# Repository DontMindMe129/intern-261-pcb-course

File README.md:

# intern-261-pcb-course

Thiết kế **ESP32-P4 DevKit** cho bài thực hành PCB. Board sử dụng **ESP32-P4 rev 1.3** làm bộ xử lý chính và **ESP32-C6** cho Wi-Fi và Bluetooth LE. PCB có **4 lớp**, kích thước **100 × 70 mm** và độ dày danh định **1,6 mm**.

## Cổng kết nối

| Cổng | Chức năng |
|---|---|
| J3 · USB-C | Nhận nguồn 5 V từ adapter |
| J5 · USB-C | Nạp và debug P4 qua USB Serial/JTAG. VBUS cũng là một đầu vào của bộ chọn nguồn. |
| J11 · USB-C | USB 2.0 High-Speed cho dữ liệu |
| J1 · Header UART | Nạp và debug ESP32-C6 |
| J4 · FFC 15 chân | Camera qua MIPI CSI-2 |
| J6 · FFC 15 chân | Màn hình qua MIPI DSI |
| J2 · microSD | Thẻ nhớ qua SDMMC 4-bit |
| J9 · RJ45 | Ethernet 10/100 qua PHY IP101GRI |
| J10 · Header loa | Loa ngoài qua ampli NS4150B |
| J7 · Header 2×12 | 13 GPIO, I²C, 3V3, 5V_SYS và GND |

Board còn có flash QSPI 16 MB, micro electret, codec ES8311, cảm biến ánh sáng VEML7700 và mạch INA226 đo dòng, áp trên nguồn hệ thống.

## Mở project KiCad

1. Dùng **KiCad 10** và cài gói **Espressif Library** qua **Plugin and Content Manager** để KiCad tra được thư viện Espressif. [Hướng dẫn cài của Espressif](https://github.com/espressif/kicad-libraries#installation-with-kicad-pcm)
2. Mở [esp32_p4_devkit.kicad_pro](hardware/esp32_p4_devkit/esp32_p4_devkit.kicad_pro) trong KiCad Project Manager. Đây là project chính để mở cả schematic và PCB.
3. Giữ nguyên cấu trúc thư mục project. `sym-lib-table` và `fp-lib-table` trỏ tới thư viện `DevKit` trong [libraries/](hardware/esp32_p4_devkit/libraries/).

## Hồ sơ thiết kế

| File | Nội dung |
|---|---|
| [BOM.xlsx](BOM.xlsx) | Danh sách linh kiện, footprint, nguồn mua và sheet DNP |
| [Sơ đồ khối Draw.io](block_diagram/esp32-p4_tong-hop.drawio) | Bản chỉnh sửa được. Xem trang **Bản hiện hành**. |
| [Tài liệu thiết kế](ESP32-P4_Hardware_Design.md) | Kiến trúc, đường nguồn, giao tiếp và bố trí PCB |
| [Design Tracker](ESP32-P4_Design_Tracker.md) | Các mục cần xác nhận trước khi đặt linh kiện, gia công và thử board |

## Trạng thái

Schematic, layout và BOM đã có trong bộ thiết kế. Cần rà ERC/DRC trên bản KiCad chính và xuất Gerber cùng file khoan từ revision chốt để gia công. Chưa có kết quả thử trên board thực.

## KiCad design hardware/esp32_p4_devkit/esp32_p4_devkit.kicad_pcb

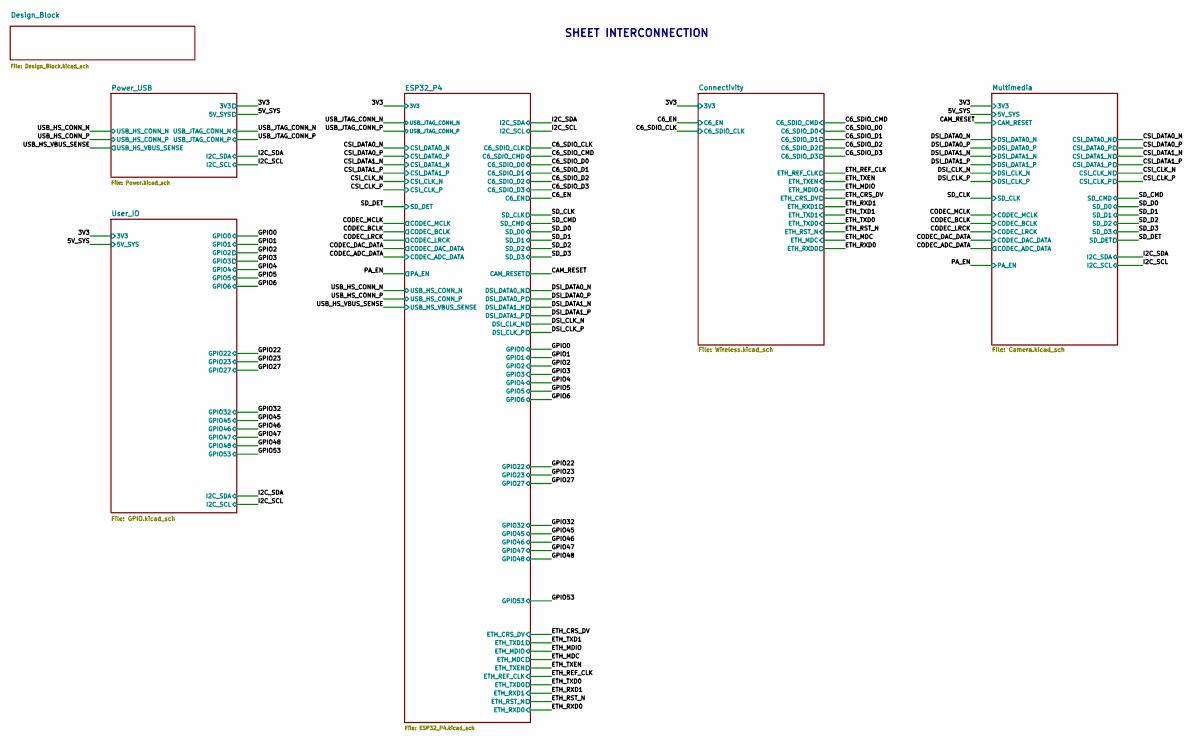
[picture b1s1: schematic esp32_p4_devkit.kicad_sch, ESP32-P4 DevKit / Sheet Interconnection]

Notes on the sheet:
SHEET INTERCONNECTION

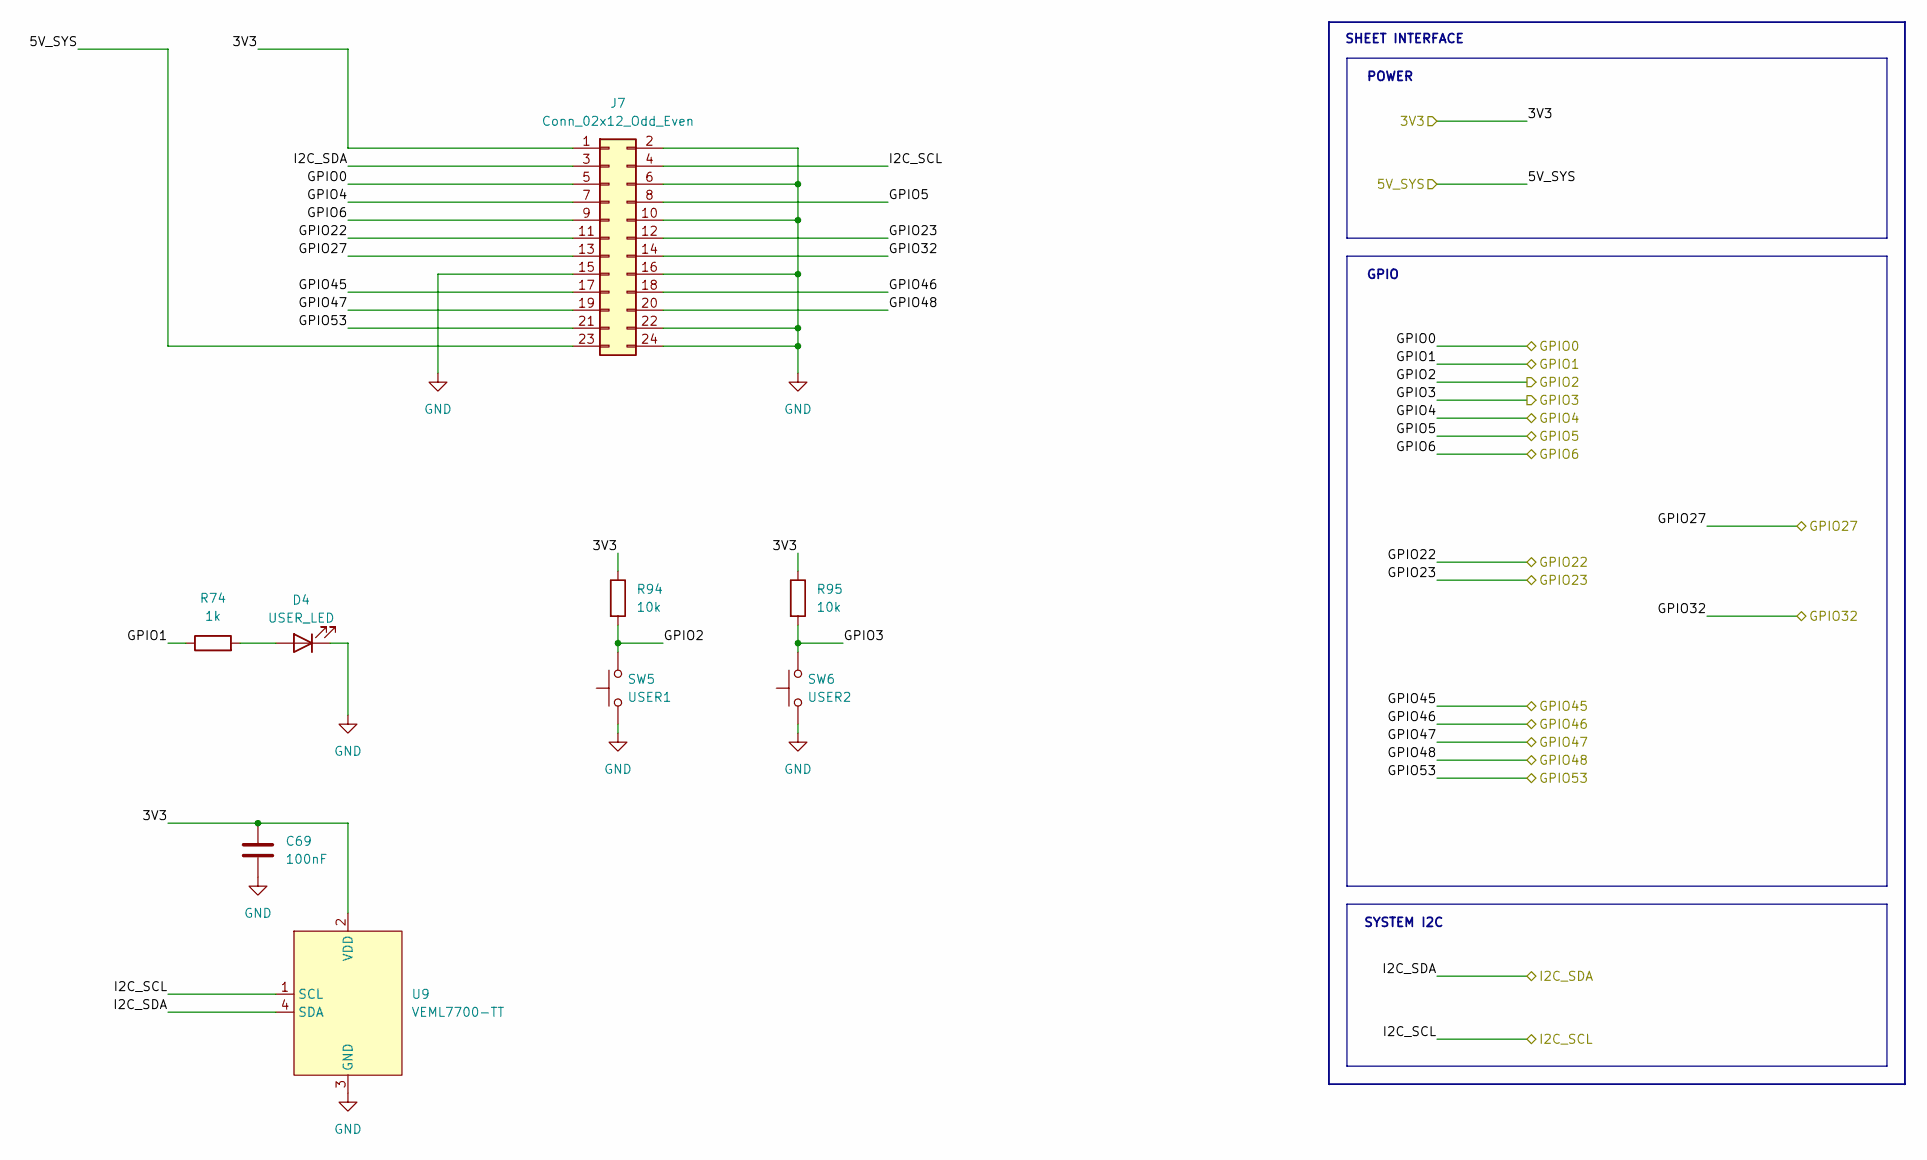
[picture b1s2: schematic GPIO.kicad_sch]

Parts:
C69: 100nF; C_0402_1005Metric; MPN CL05B104KO5NNNC
D4: USER_LED; LED_0603_1608Metric; MPN LTST-C190KGKT
J7: Conn_02x12_Odd_Even; PinHeader_2x12_P2.54mm_Vertical
R74: 1k; R_0603_1608Metric; MPN ERJ-3EKF1001V
R94, R95: 10k; R_0603_1608Metric; MPN ERJ-3EKF1002V
SW5: USER1; SW_SPST_TL3305A; MPN TL3305AF160QG
SW6: USER2; SW_SPST_TL3305A; MPN TL3305AF160QG
U9: VEML7700-TT; SMT_L7700-TT_VIS; MPN VEML7700-TT

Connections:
/3V3: C69.1, J7.1, R94.1, R95.1, U9.2 (VDD); also elsewhere on the board
/5V_SYS: J7.23; also elsewhere on the board
/GPIO0: J7.5; also elsewhere on the board
/GPIO1: R74.1; also elsewhere on the board
/GPIO2: R94.2, SW5.2; also elsewhere on the board
/GPIO3: R95.2, SW6.2; also elsewhere on the board
/GPIO4: J7.7; also elsewhere on the board
/GPIO5: J7.8; also elsewhere on the board
/GPIO6: J7.9; also elsewhere on the board
/GPIO22: J7.11; also elsewhere on the board
/GPIO23: J7.12; also elsewhere on the board
/GPIO27: J7.13; also elsewhere on the board
/GPIO32: J7.14; also elsewhere on the board
/GPIO45: J7.17; also elsewhere on the board
/GPIO46: J7.18; also elsewhere on the board
/GPIO47: J7.19; also elsewhere on the board
/GPIO48: J7.20; also elsewhere on the board
/GPIO53: J7.21; also elsewhere on the board
/I2C_SCL: J7.4, U9.1 (SCL); also elsewhere on the board
/I2C_SDA: J7.3, U9.4 (SDA); also elsewhere on the board
GND: C69.2, D4.1 (K), J7.2, J7.6, J7.10, J7.15, J7.16, J7.22, J7.24, SW5.1, SW6.1, U9.3 (GND); also elsewhere on the board
unnamed: D4.2 (A), R74.2

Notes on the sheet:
SHEET INTERFACE
GPIO
POWER
SYSTEM I2C

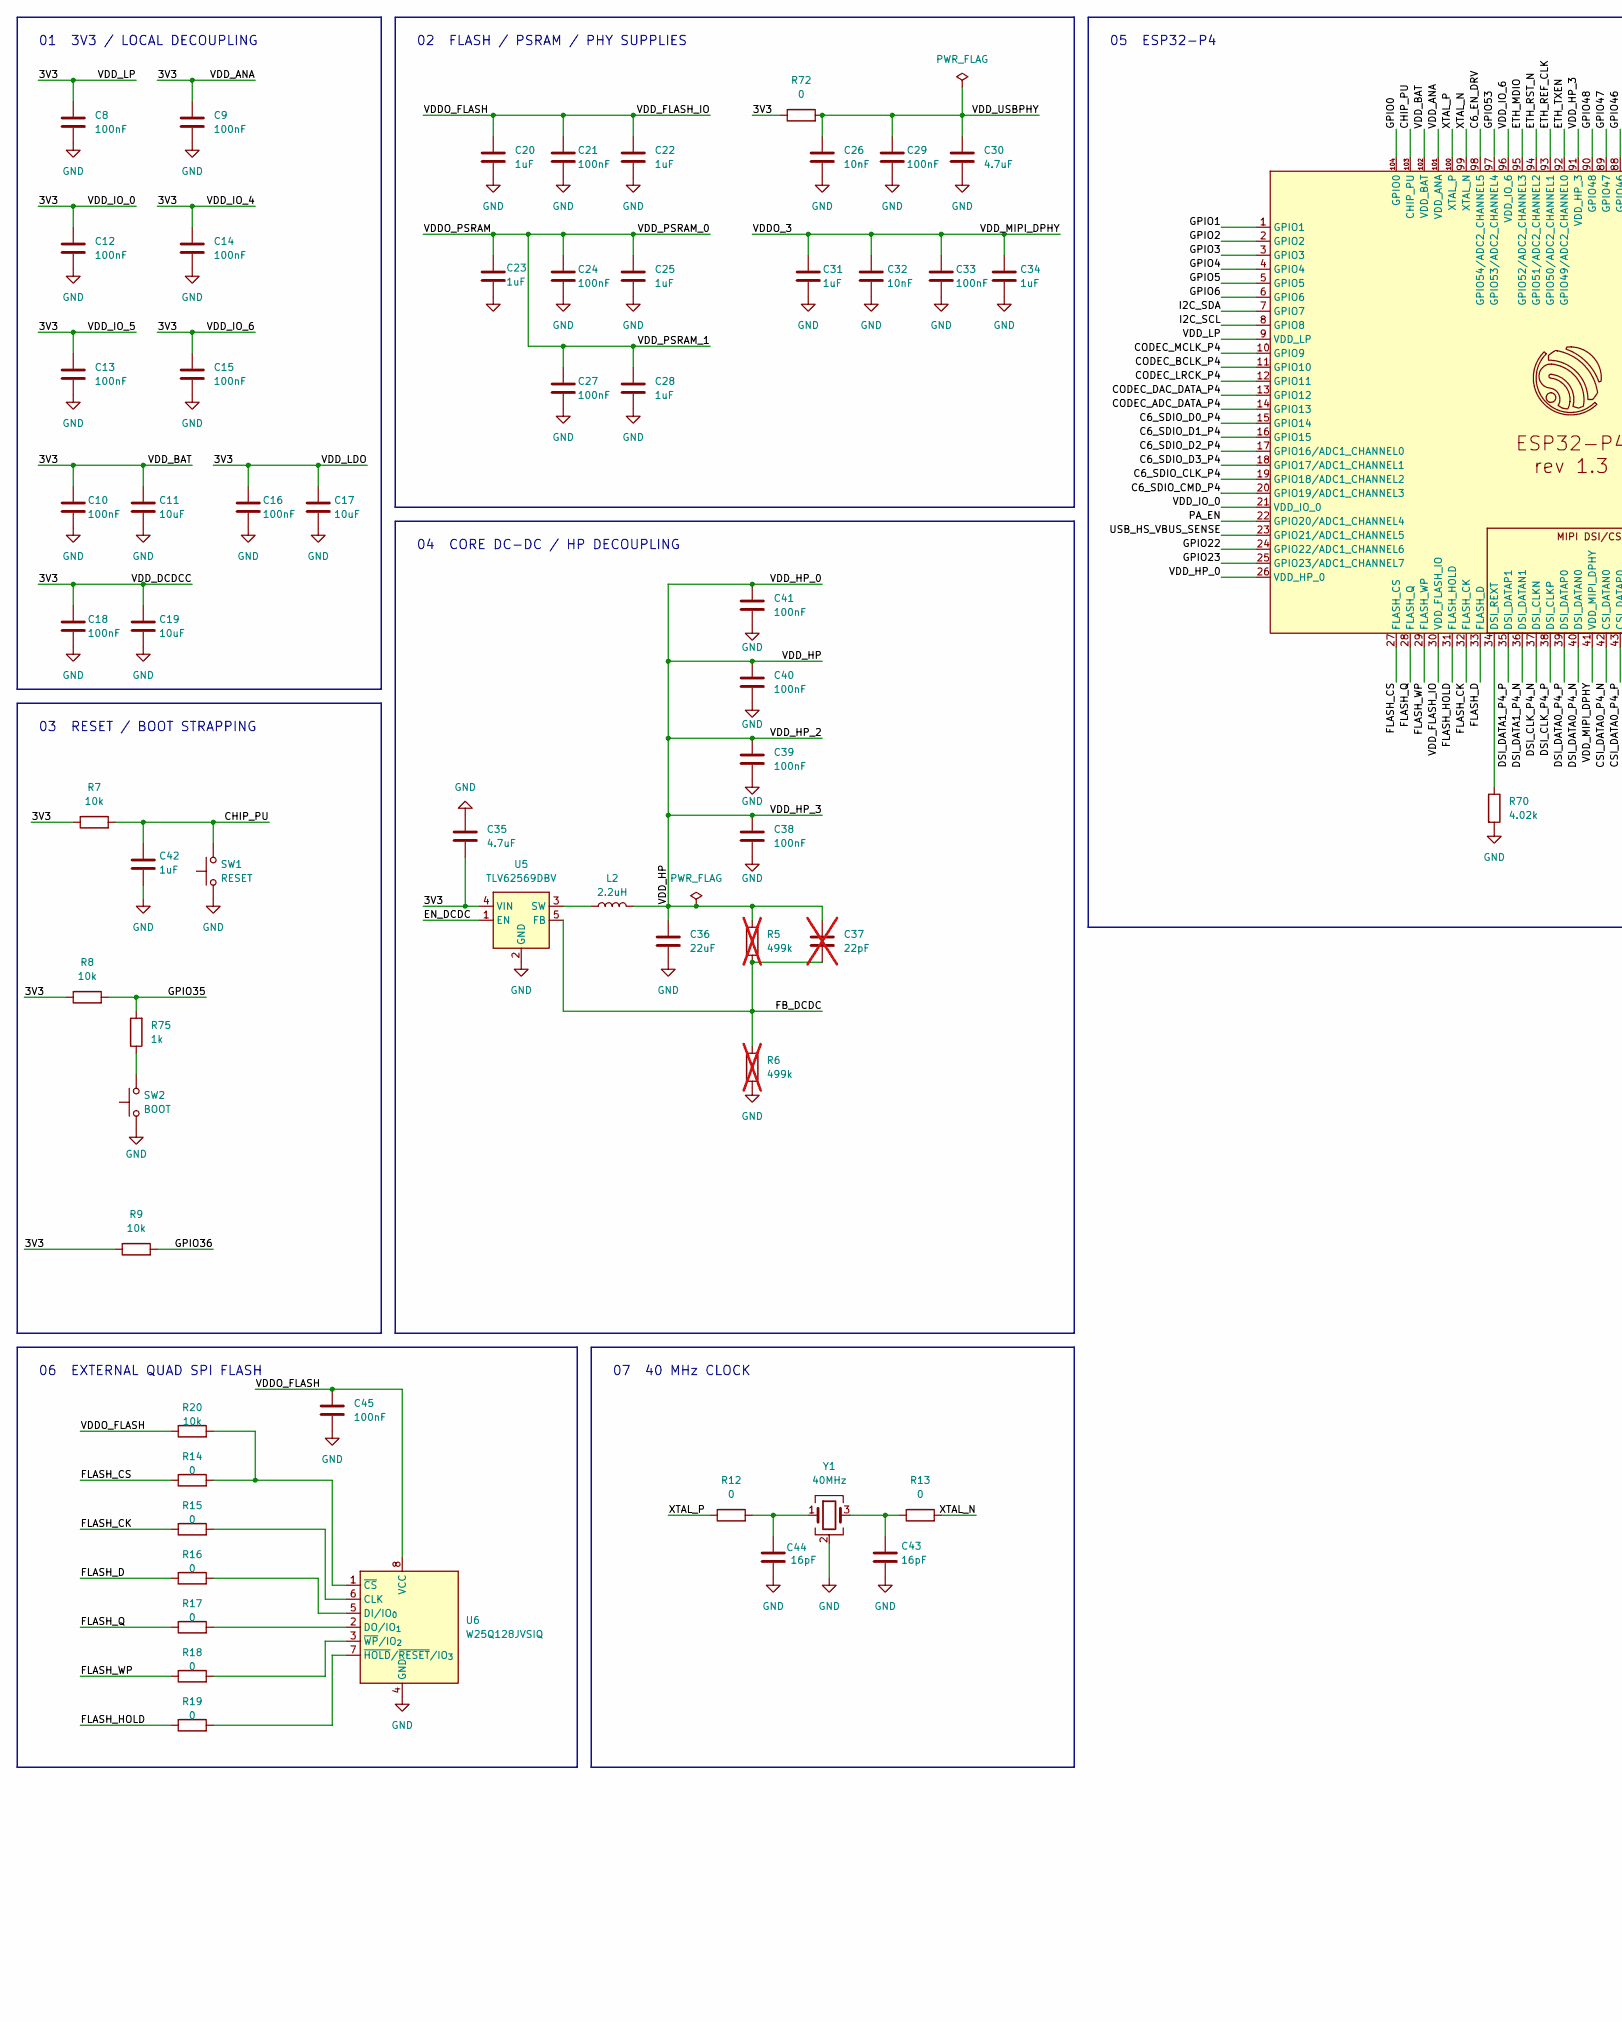
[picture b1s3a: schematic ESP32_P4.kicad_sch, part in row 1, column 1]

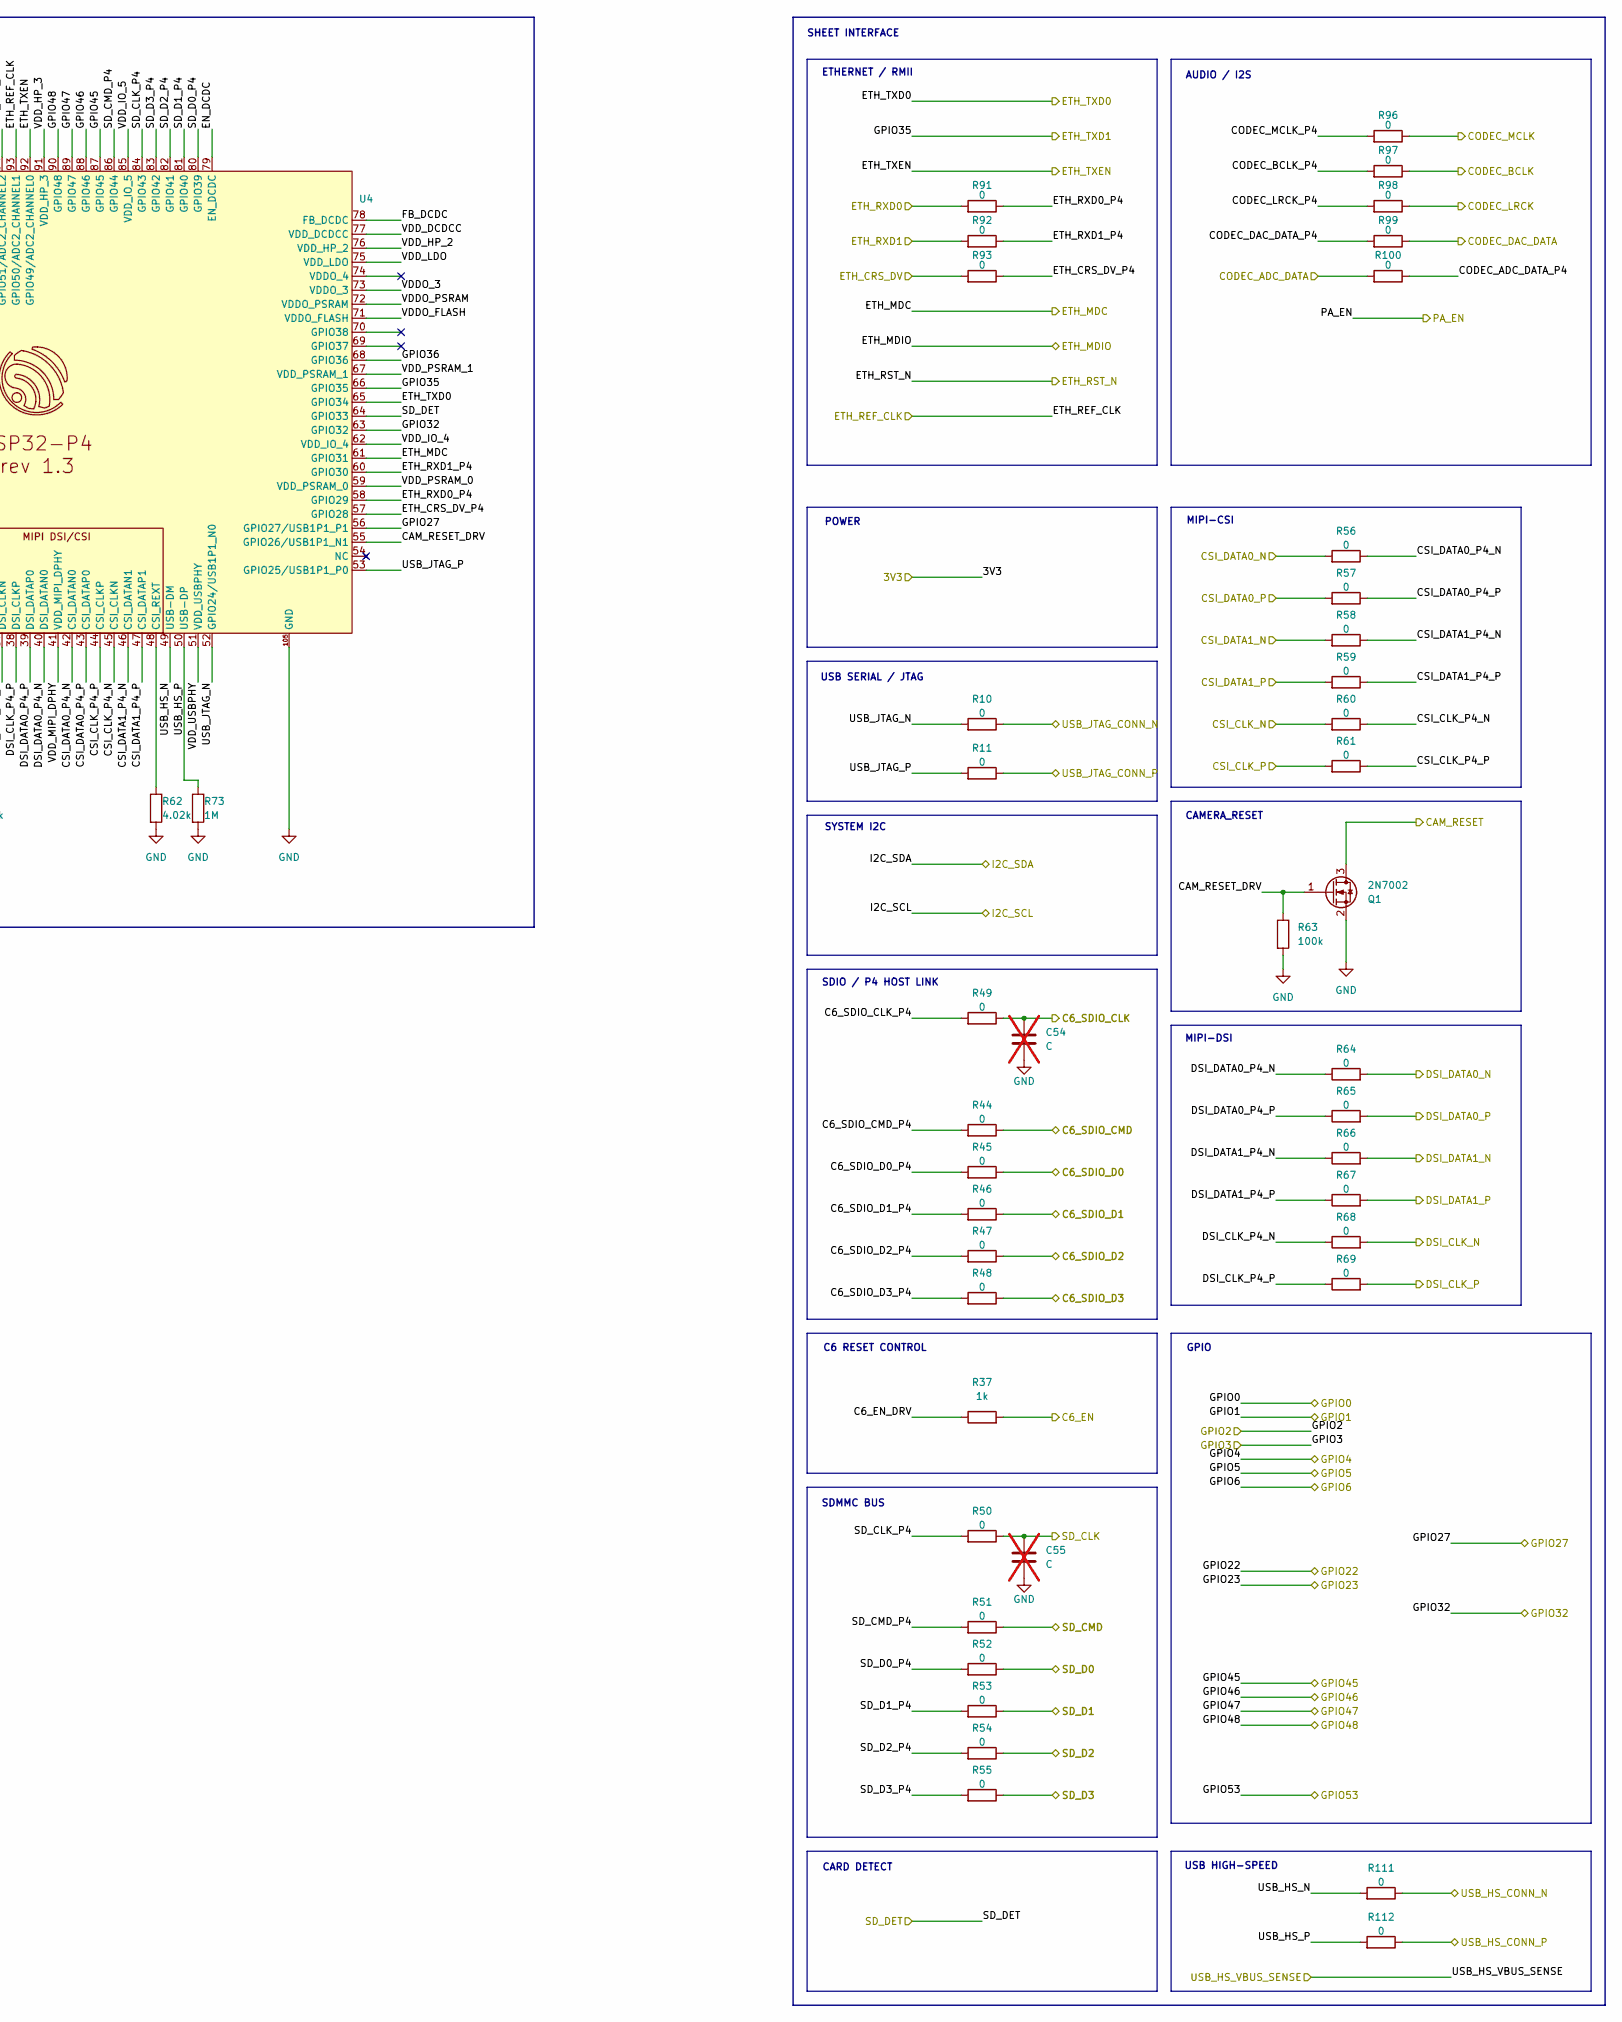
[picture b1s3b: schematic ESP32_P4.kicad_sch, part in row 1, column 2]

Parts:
C8, C9, C10, C12, C13, C14, C15, C16, C18, C21, C24, C27, C29, C33, C38, C40, C41, C45: 100nF; C_0402_1005Metric; MPN CL05B104KO5NNNC
C11, C17, C19: 10uF; C_1206_3216Metric; MPN GRM31CR71E106MA12L
C20, C22, C23, C25, C28, C31, C34, C42: 1uF; C_0805_2012Metric; MPN GRM21BR71C105KA01L
C26, C32: 10nF; C_0402_1005Metric; MPN CL05B103KB5NNNC
C30: 4.7uF; C_0805_2012Metric; MPN GRM21BR71C475KE51L
C35: 4.7uF; C_0805_2012Metric; MPN CL21A475KPFNNNE
C36: 22uF; C_1206_3216Metric; MPN CL31A226KOCLNNC
C37: 22pF; C_0603_1608Metric; not fitted
C39: 100nF; C_0603_1608Metric; MPN CL10B104KB8NFNC
C43, C44: 16pF; C_0603_1608Metric; MPN CC0603JRNPO9BN160
C54, C55: C; C_0603_1608Metric; not fitted
L2: 2.2uH; L_Abracon_ASPI-0630LR; MPN ASPI-0630LR-2R2M-T15
Q1: 2N7002; SOT-23; MPN 2N7002,215
R5, R6: 499k; R_0603_1608Metric; not fitted
R7, R8, R9, R20: 10k; R_0603_1608Metric; MPN ERJ-3EKF1002V
R10, R11, R12, R13, R14, R15, R16, R17, R18, R19, R44, R45, R46, R47, R48, R49, R50, R51, R52, R53, R54, R55, R56, R57, R58, R59, R60, R61, R64, R65, R66, R67, R68, R69, R72, R91, R92, R93, R96, R97, R98, R99, R100, R111, R112: 0; R_0603_1608Metric; MPN ERJ-3GEY0R00V
R37, R75: 1k; R_0603_1608Metric; MPN ERJ-3EKF1001V
R62, R70: 4.02k; R_0603_1608Metric; MPN CRCW06034K02FKEA
R63: 100k; R_0603_1608Metric; MPN CRCW0603100KFKEA
R73: 1M; R_0603_1608Metric; MPN ERJ-3EKF1004V
SW1: RESET; SW_SPST_TL3305A; MPN TL3305AF160QG
SW2: BOOT; SW_SPST_TL3305A; MPN TL3305AF160QG
U4: ESP32-P4 (rev 1.3); ESP32-P4; MPN ESP32-P4NRW32
U5: TLV62569DBV; SOT-23-5; MPN TLV62569DBVR
U6: W25Q128JVSIQ; SOIC-8_5.3x5.3mm_P1.27mm; MPN W25Q128JVSIQ
Y1: 40MHz; Crystal_SMD_3225-4Pin_3.2x2.5mm; MPN ABM8-40.000MHZ-10-1-U-T

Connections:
/3V3: C8.1, C9.1, C10.1, C11.1, C12.1, C13.1, C14.1, C15.1, C16.1, C17.1, C18.1, C19.1, C35.2, R7.1, R8.1, R9.1, R72.1, U4.9 (VDD_LP), U4.21 (VDD_IO_0), U4.62 (VDD_IO_4), U4.75 (VDD_LDO), U4.77 (VDD_DCDCC), U4.85 (VDD_IO_5), U4.96 (VDD_IO_6), U4.101 (VDD_ANA), U4.102 (VDD_BAT), U5.4 (VIN); also elsewhere on the board
/C6_EN: R37.2; also elsewhere on the board
/C6_SDIO_CLK: C54.1, R49.1; also elsewhere on the board
/C6_SDIO_CMD: R44.1; also elsewhere on the board
/C6_SDIO_D0: R45.1; also elsewhere on the board
/C6_SDIO_D1: R46.1; also elsewhere on the board
/C6_SDIO_D2: R47.1; also elsewhere on the board
/C6_SDIO_D3: R48.1; also elsewhere on the board
/CAM_RESET: Q1.3 (D); also elsewhere on the board
/CODEC_ADC_DATA: R100.2; also elsewhere on the board
/CODEC_BCLK: R97.1; also elsewhere on the board
/CODEC_DAC_DATA: R99.1; also elsewhere on the board
/CODEC_LRCK: R98.1; also elsewhere on the board
/CODEC_MCLK: R96.1; also elsewhere on the board
/CSI_CLK_N: R60.2; also elsewhere on the board
/CSI_CLK_P: R61.2; also elsewhere on the board
/CSI_DATA0_N: R56.2; also elsewhere on the board
/CSI_DATA0_P: R57.2; also elsewhere on the board
/CSI_DATA1_N: R58.2; also elsewhere on the board
/CSI_DATA1_P: R59.2; also elsewhere on the board
/DSI_CLK_N: R68.2; also elsewhere on the board
/DSI_CLK_P: R69.2; also elsewhere on the board
/DSI_DATA0_N: R64.2; also elsewhere on the board
/DSI_DATA0_P: R65.2; also elsewhere on the board
/DSI_DATA1_N: R66.2; also elsewhere on the board
/DSI_DATA1_P: R67.2; also elsewhere on the board
/ESP32_P4/C6_EN_DRV: R37.1, U4.98 (GPIO54/ADC2_CHANNEL5)
/ESP32_P4/C6_SDIO_CLK_P4: R49.2, U4.19 (GPIO18/ADC1_CHANNEL2)
/ESP32_P4/C6_SDIO_CMD_P4: R44.2, U4.20 (GPIO19/ADC1_CHANNEL3)
/ESP32_P4/C6_SDIO_D0_P4: R45.2, U4.15 (GPIO14)
/ESP32_P4/C6_SDIO_D1_P4: R46.2, U4.16 (GPIO15)
/ESP32_P4/C6_SDIO_D2_P4: R47.2, U4.17 (GPIO16/ADC1_CHANNEL0)
/ESP32_P4/C6_SDIO_D3_P4: R48.2, U4.18 (GPIO17/ADC1_CHANNEL1)
/ESP32_P4/CAM_RESET_DRV: Q1.1 (G), R63.1, U4.55 (GPIO26/USB1P1_N1)
/ESP32_P4/CHIP_PU: C42.1, R7.2, SW1.2, U4.103 (CHIP_PU)
/ESP32_P4/CODEC_ADC_DATA_P4: R100.1, U4.14 (GPIO13)
/ESP32_P4/CODEC_BCLK_P4: R97.2, U4.11 (GPIO10)
/ESP32_P4/CODEC_DAC_DATA_P4: R99.2, U4.13 (GPIO12)
/ESP32_P4/CODEC_LRCK_P4: R98.2, U4.12 (GPIO11)
/ESP32_P4/CODEC_MCLK_P4: R96.2, U4.10 (GPIO9)
/ESP32_P4/CSI_CLK_P4_N: R60.1, U4.45 (CSI_CLKN)
/ESP32_P4/CSI_CLK_P4_P: R61.1, U4.44 (CSI_CLKP)
/ESP32_P4/CSI_DATA0_P4_N: R56.1, U4.42 (CSI_DATAN0)
/ESP32_P4/CSI_DATA0_P4_P: R57.1, U4.43 (CSI_DATAP0)
/ESP32_P4/CSI_DATA1_P4_N: R58.1, U4.46 (CSI_DATAN1)
/ESP32_P4/CSI_DATA1_P4_P: R59.1, U4.47 (CSI_DATAP1)
/ESP32_P4/DSI_CLK_P4_N: R68.1, U4.37 (DSI_CLKN)
/ESP32_P4/DSI_CLK_P4_P: R69.1, U4.38 (DSI_CLKP)
/ESP32_P4/DSI_DATA0_P4_N: R64.1, U4.40 (DSI_DATAN0)
/ESP32_P4/DSI_DATA0_P4_P: R65.1, U4.39 (DSI_DATAP0)
/ESP32_P4/DSI_DATA1_P4_N: R66.1, U4.36 (DSI_DATAN1)
/ESP32_P4/DSI_DATA1_P4_P: R67.1, U4.35 (DSI_DATAP1)
/ESP32_P4/EN_DCDC: U4.79 (EN_DCDC), U5.1 (EN)
/ESP32_P4/ETH_CRS_DV_P4: R93.1, U4.57 (GPIO28)
/ESP32_P4/ETH_RXD0_P4: R91.1, U4.58 (GPIO29)
/ESP32_P4/ETH_RXD1_P4: R92.1, U4.60 (GPIO30)
/ESP32_P4/FB_DCDC: C37.2, R5.2, R6.1, U4.78 (FB_DCDC), U5.5 (FB)
/ESP32_P4/FLASH_CK: R15.1, U4.32 (FLASH_CK)
/ESP32_P4/FLASH_CS: R14.1, U4.27 (FLASH_CS)
/ESP32_P4/FLASH_D: R16.1, U4.33 (FLASH_D)
/ESP32_P4/FLASH_HOLD: R19.1, U4.31 (FLASH_HOLD)
/ESP32_P4/FLASH_Q: R17.1, U4.28 (FLASH_Q)
/ESP32_P4/FLASH_WP: R18.1, U4.29 (FLASH_WP)
/ESP32_P4/GPIO36: R9.2, U4.68 (GPIO36)
/ESP32_P4/SD_CLK_P4: R50.2, U4.84 (GPIO43)
/ESP32_P4/SD_CMD_P4: R51.2, U4.86 (GPIO44)
/ESP32_P4/SD_D0_P4: R52.2, U4.80 (GPIO39)
/ESP32_P4/SD_D1_P4: R53.2, U4.81 (GPIO40)
/ESP32_P4/SD_D2_P4: R54.2, U4.82 (GPIO41)
/ESP32_P4/SD_D3_P4: R55.2, U4.83 (GPIO42)
/ESP32_P4/USB_HS_N: R111.2, U4.49 (USB-DM)
/ESP32_P4/USB_HS_P: R73.1, R112.2, U4.50 (USB-DP)
/ESP32_P4/USB_JTAG_N: R10.2, U4.52 (GPIO24/USB1P1_N0)
/ESP32_P4/USB_JTAG_P: R11.2, U4.53 (GPIO25/USB1P1_P0)
/ESP32_P4/VDDO_3: C31.1, C32.1, C33.1, C34.1, U4.41 (VDD_MIPI_DPHY), U4.73 (VDDO_3)
/ESP32_P4/VDDO_FLASH: C20.1, C21.1, C22.1, C45.1, R20.1, U4.30 (VDD_FLASH_IO), U4.71 (VDDO_FLASH), U6.8 (VCC)
/ESP32_P4/VDDO_PSRAM: C23.1, C24.1, C25.1, C27.1, C28.1, U4.59 (VDD_PSRAM_0), U4.67 (VDD_PSRAM_1), U4.72 (VDDO_PSRAM)
/ESP32_P4/VDD_HP: C36.1, C37.1, C38.1, C39.1, C40.1, C41.1, L2.2, R5.1, U4.26 (VDD_HP_0), U4.76 (VDD_HP_2), U4.91 (VDD_HP_3)
/ESP32_P4/VDD_USBPHY: C26.1, C29.1, C30.1, R72.2, U4.51 (VDD_USBPHY)
/ESP32_P4/XTAL_N: R13.2, U4.99 (XTAL_N)
/ESP32_P4/XTAL_P: R12.1, U4.100 (XTAL_P)
/ETH_CRS_DV: R93.2; also elsewhere on the board
/ETH_MDC: U4.61 (GPIO31); also elsewhere on the board
/ETH_MDIO: U4.95 (GPIO52/ADC2_CHANNEL3); also elsewhere on the board
/ETH_REF_CLK: U4.93 (GPIO50/ADC2_CHANNEL1); also elsewhere on the board
/ETH_RST_N: U4.94 (GPIO51/ADC2_CHANNEL2); also elsewhere on the board
/ETH_RXD0: R91.2; also elsewhere on the board
/ETH_RXD1: R92.2; also elsewhere on the board
/ETH_TXD0: U4.65 (GPIO34); also elsewhere on the board
/ETH_TXD1: R8.2, R75.2, U4.66 (GPIO35); also elsewhere on the board
/ETH_TXEN: U4.92 (GPIO49/ADC2_CHANNEL0); also elsewhere on the board
/GPIO0: U4.104 (GPIO0); also elsewhere on the board
/GPIO1: U4.1 (GPIO1); also elsewhere on the board
/GPIO2: U4.2 (GPIO2); also elsewhere on the board
/GPIO3: U4.3 (GPIO3); also elsewhere on the board
/GPIO4: U4.4 (GPIO4); also elsewhere on the board
/GPIO5: U4.5 (GPIO5); also elsewhere on the board
/GPIO6: U4.6 (GPIO6); also elsewhere on the board
/GPIO22: U4.24 (GPIO22/ADC1_CHANNEL6); also elsewhere on the board
/GPIO23: U4.25 (GPIO23/ADC1_CHANNEL7); also elsewhere on the board
/GPIO27: U4.56 (GPIO27/USB1P1_P1); also elsewhere on the board
/GPIO32: U4.63 (GPIO32); also elsewhere on the board
/GPIO45: U4.87 (GPIO45); also elsewhere on the board
/GPIO46: U4.88 (GPIO46); also elsewhere on the board
/GPIO47: U4.89 (GPIO47); also elsewhere on the board
/GPIO48: U4.90 (GPIO48); also elsewhere on the board
/GPIO53: U4.97 (GPIO53/ADC2_CHANNEL4); also elsewhere on the board
/I2C_SCL: U4.8 (GPIO8); also elsewhere on the board
/I2C_SDA: U4.7 (GPIO7); also elsewhere on the board
/PA_EN: U4.22 (GPIO20/ADC1_CHANNEL4); also elsewhere on the board
/SD_CLK: C55.1, R50.1; also elsewhere on the board
/SD_CMD: R51.1; also elsewhere on the board
/SD_D0: R52.1; also elsewhere on the board
/SD_D1: R53.1; also elsewhere on the board
/SD_D2: R54.1; also elsewhere on the board
/SD_D3: R55.1; also elsewhere on the board
/SD_DET: U4.64 (GPIO33); also elsewhere on the board
/USB_HS_CONN_N: R111.1; also elsewhere on the board
/USB_HS_CONN_P: R112.1; also elsewhere on the board
/USB_HS_VBUS_SENSE: U4.23 (GPIO21/ADC1_CHANNEL5); also elsewhere on the board
/USB_JTAG_CONN_N: R10.1; also elsewhere on the board
/USB_JTAG_CONN_P: R11.1; also elsewhere on the board
GND: C8.2, C9.2, C10.2, C11.2, C12.2, C13.2, C14.2, C15.2, C16.2, C17.2, C18.2, C19.2, C20.2, C21.2, C22.2, C23.2, C24.2, C25.2, C26.2, C27.2, C28.2, C29.2, C30.2, C31.2, C32.2, C33.2, C34.2, C35.1, C36.2, C38.2, C39.2, C40.2, C41.2, C42.2, C43.2, C44.2, C45.2, C54.2, C55.2, Q1.2 (S), R6.2, R62.2, R63.2, R70.2, R73.2, SW1.1, SW2.1, U4.105 (GND), U5.2 (GND), U6.4 (GND), Y1.2 (G), Y1.4 (G); also elsewhere on the board
unnamed: C43.1, R13.1, Y1.3
unnamed: C44.1, R12.2, Y1.1
unnamed: R75.1, SW2.2
unnamed: R62.1, U4.48 (CSI_REXT)
unnamed: R70.1, U4.34 (DSI_REXT)
unnamed: L2.1, U5.3 (SW)
unnamed: R15.2, U6.6 (CLK)
unnamed: R16.2, U6.5 (DI/IO_{0})
unnamed: R17.2, U6.2 (DO/IO_{1})
unnamed: R14.2, R20.2, U6.1 (~CS)
unnamed: R19.2, U6.7 (~HOLD/~RESET/IO_{3})
unnamed: R18.2, U6.3 (~WP/IO_{2})

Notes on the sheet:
CARD DETECT
USB HIGH-SPEED
SDIO / P4 HOST LINK
05 ESP32-P4
USB SERIAL / JTAG
AUDIO / I2S
06 EXTERNAL QUAD SPI FLASH
SHEET INTERFACE
SYSTEM I2C
CAMERA_RESET
SDMMC BUS
02 FLASH / PSRAM / PHY SUPPLIES
POWER
MIPI-DSI
03 RESET / BOOT STRAPPING
ETHERNET / RMII
GPIO
MIPI-CSI
01 3V3 / LOCAL DECOUPLING
04 CORE DC-DC / HP DECOUPLING
C6 RESET CONTROL
07 40 MHz CLOCK
